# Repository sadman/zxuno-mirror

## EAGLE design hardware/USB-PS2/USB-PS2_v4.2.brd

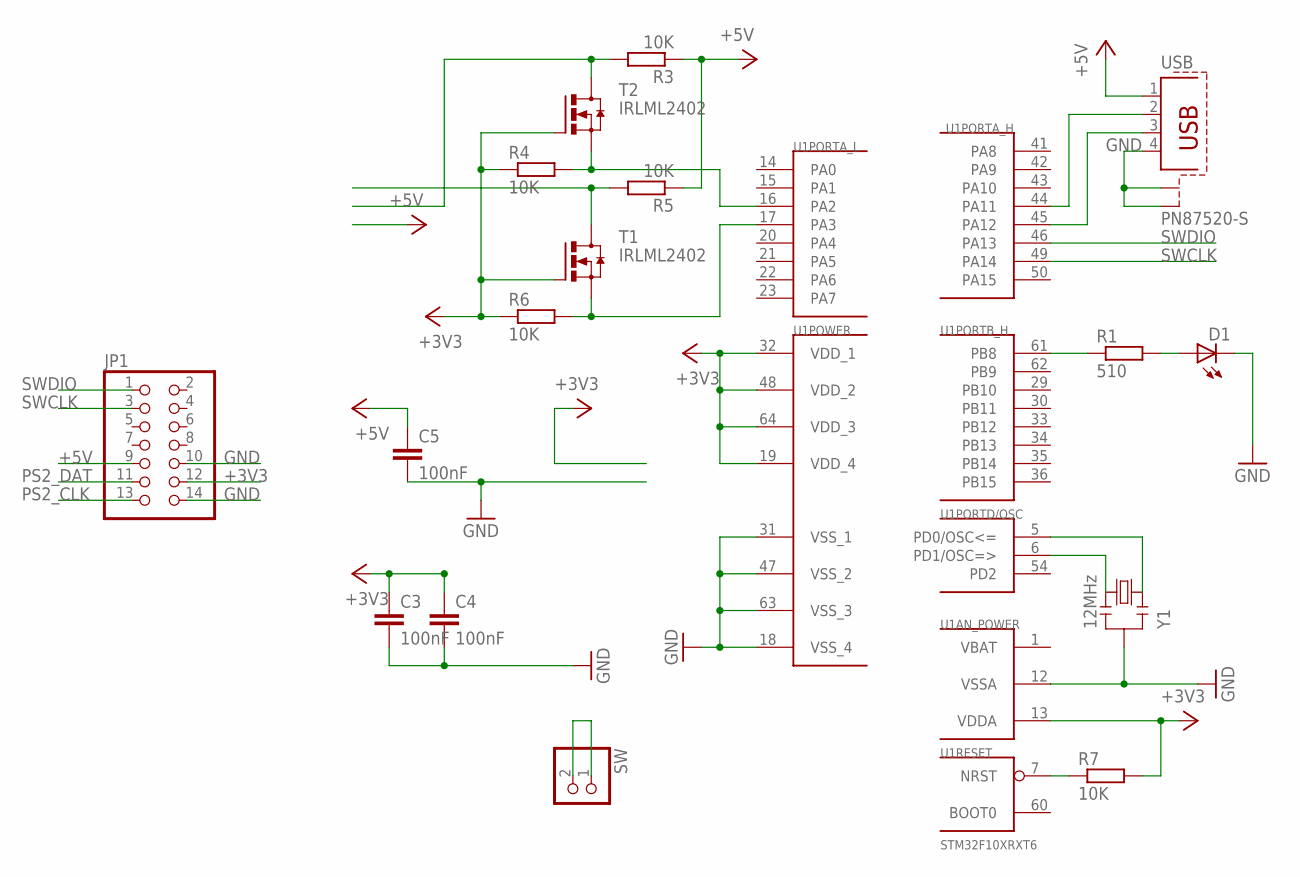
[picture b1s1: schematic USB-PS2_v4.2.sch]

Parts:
C3, C4, C5: 100nF; C0805
D1: LEDSML0805; SML0805
JP1: PINHD-2X7; 2X07
R1: 510; R0805
R3, R4, R5, R6, R7: 10K; R0805
SW: PINHD-1X2; 1X02
T1, T2: IRLML2402; MICRO3
U1: STM32F10XRXT6; TQFP64
USB: PN87520-S
Y1: 12MHz; RESONATOR

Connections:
+3V3: C3.1, C4.1, JP1.12, R4.1, R6.1, R7.2, T1.1 (G), T2.1 (G), U1.13 (VDDA), U1.19 (VDD_4), U1.32 (VDD_1), U1.48 (VDD_2), U1.64 (VDD_3)
+5V: C5.1, JP1.9, R3.1, R5.1, USB.1
GND: C3.2, C4.2, C5.2, D1.C, JP1.10, JP1.14, U1.12 (VSSA), U1.18 (VSS_4), U1.31 (VSS_1), U1.47 (VSS_2), U1.63 (VSS_3), USB.4, USB.S1, USB.S2, Y1.2
unnamed: U1.44 (PA11), USB.2
unnamed: U1.45 (PA12), USB.3
unnamed: R1.1, U1.61 (PB8)
unnamed: U1.5 (PD0/OSC<=), Y1.1
unnamed: D1.A, R1.2
unnamed: U1.6 (PD1/OSC=>), Y1.3
unnamed: R7.1, U1.7 (NRST)
unnamed: SW.1, SW.2
unnamed: R6.2, T1.2 (S), U1.17 (PA3)
unnamed: R4.2, T2.2 (S), U1.16 (PA2)
PS2_CLK: JP1.13, R5.2, T1.3 (D)
PS2_DAT: JP1.11, R3.2, T2.3 (D)
SWCLK: JP1.3, U1.49 (PA14)
SWDIO: JP1.1, U1.46 (PA13)
VBAT: U1.1 (VBAT)

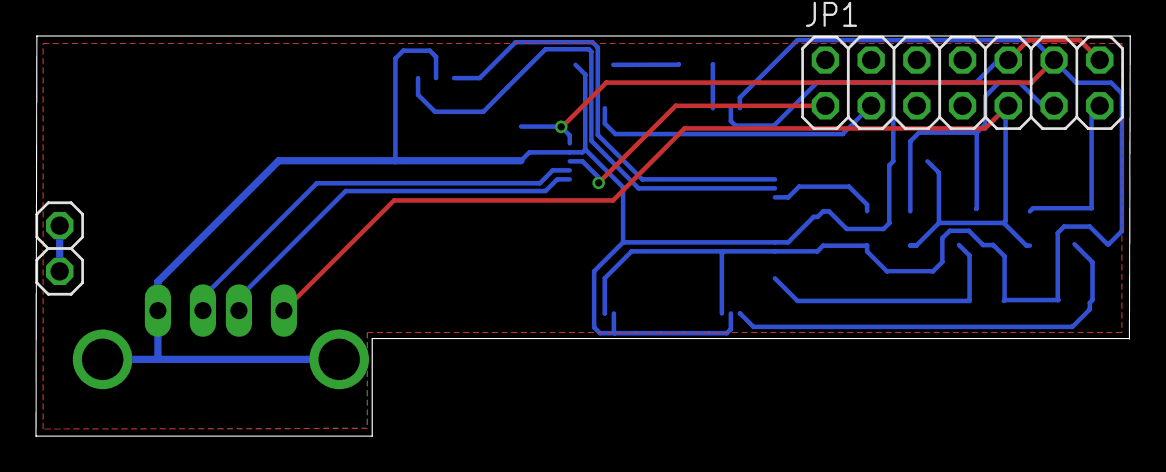
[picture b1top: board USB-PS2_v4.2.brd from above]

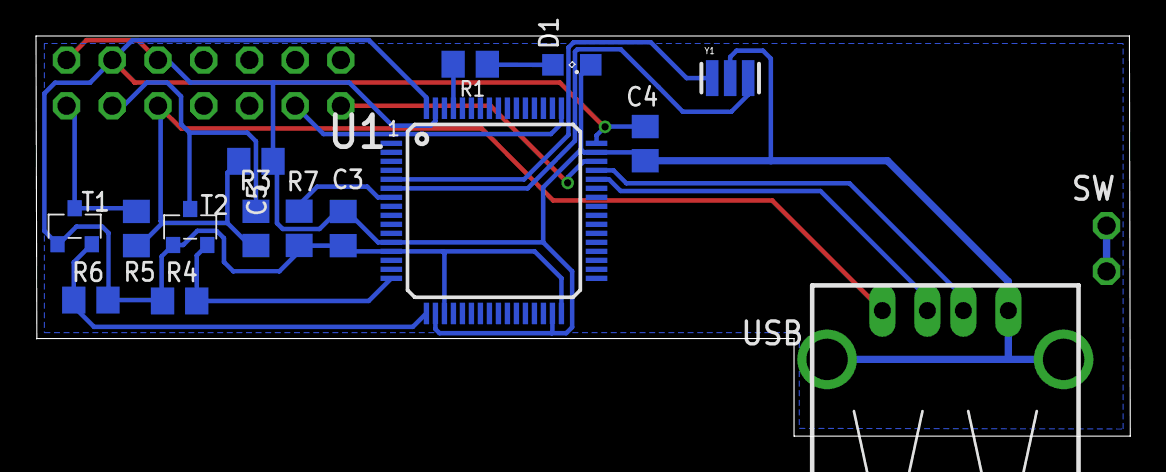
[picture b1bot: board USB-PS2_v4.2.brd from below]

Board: 2 copper layers, 60.8 x 22.2 mm, 17 parts (15 on the bottom side), 17 nets.

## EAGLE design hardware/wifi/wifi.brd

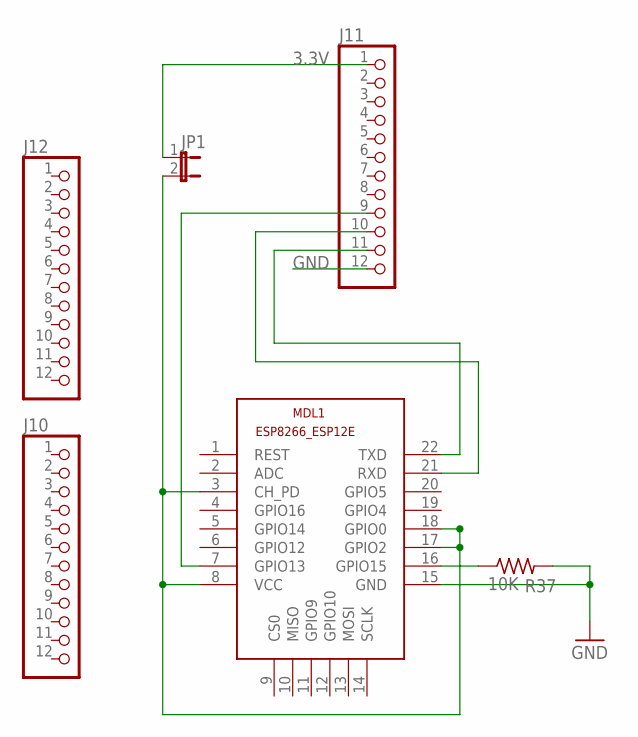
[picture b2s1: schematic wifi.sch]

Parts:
J10, J11, J12: PINHD-1X12; 1X12
JP1: JP1E; JP1
MDL1: ESP8266-12EESP8266-ESP12E; ESP8266-ESP12E
R37: 10K; R0805

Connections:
3.3V: J11.1, JP1.1
GND: J11.12, MDL1.15 (GND), R37.2
unnamed: MDL1.16 (GPIO15), R37.1
unnamed: J11.9, MDL1.7 (GPIO13)
unnamed: J11.10, MDL1.21 (RXD)
unnamed: J11.11, MDL1.22 (TXD)
VIN: JP1.2, MDL1.3 (CH_PD), MDL1.8 (VCC), MDL1.17 (GPIO2), MDL1.18 (GPIO0)

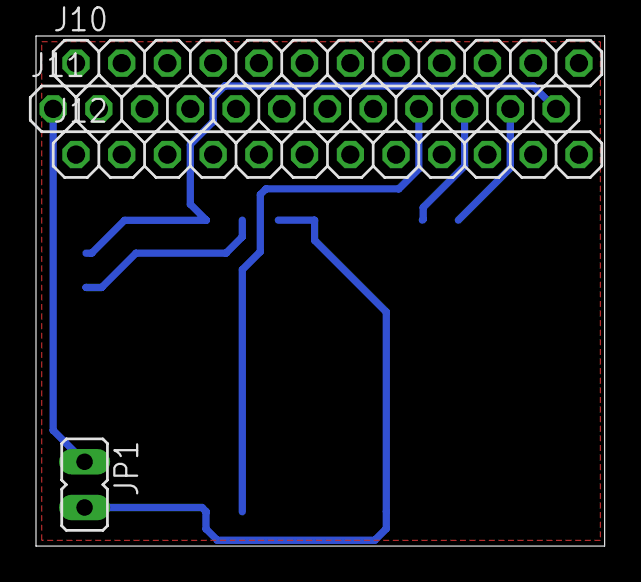
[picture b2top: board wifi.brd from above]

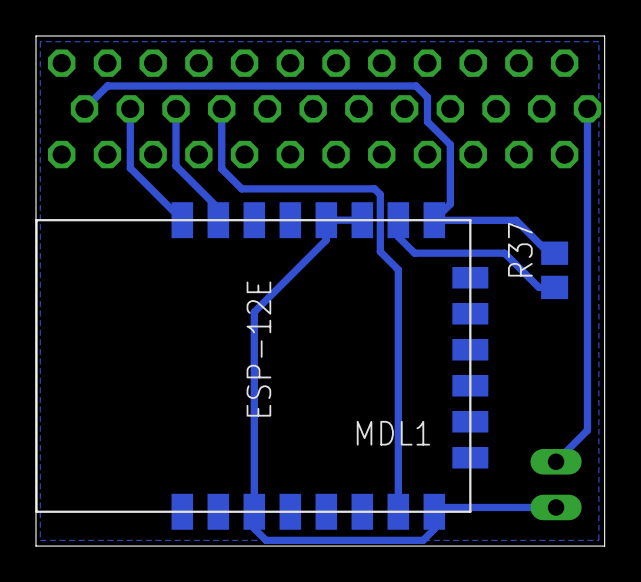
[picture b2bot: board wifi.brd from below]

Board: 2 copper layers, 31.6 x 28.3 mm, 6 parts (2 on the bottom side), 7 nets.

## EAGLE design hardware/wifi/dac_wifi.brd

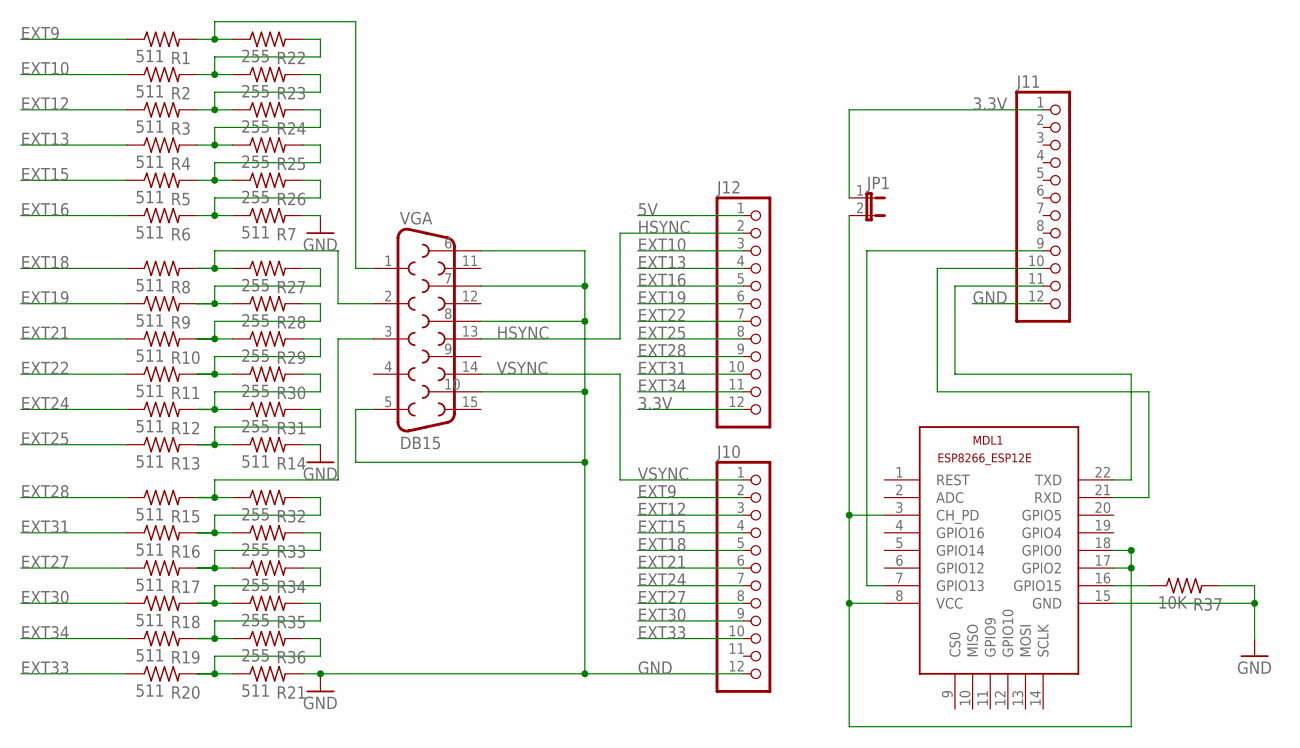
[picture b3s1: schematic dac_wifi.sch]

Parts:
J10, J11, J12: PINHD-1X12; 1X12
JP1: JP1E; JP1
MDL1: ESP8266-12EESP8266-ESP12E; ESP8266-ESP12E
R1, R2, R3, R4, R5, R6, R7, R8, R9, R10, R11, R12, R13, R14, R15, R16, R17, R18, R19, R20, R21: 511; R0805
R22, R23, R24, R25, R26, R27, R28, R29, R30, R31, R32, R33, R34, R35, R36: 255; R0805
R37: 10K; R0805
VGA: DB15

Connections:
3.3V: J11.1, J12.12, JP1.1
5V: J12.1
EXT9: J10.2, R1.1
EXT10: J12.3, R2.1
EXT12: J10.3, R3.1
EXT13: J12.4, R4.1
EXT15: J10.4, R5.1
EXT16: J12.5, R6.1
EXT18: J10.5, R8.1
EXT19: J12.6, R9.1
EXT21: J10.6, R10.1
EXT22: J12.7, R11.1
EXT24: J10.7, R12.1
EXT25: J12.8, R13.1
EXT27: J10.8, R17.1
EXT28: J12.9, R15.1
EXT30: J10.9, R18.1
EXT31: J12.10, R16.1
EXT33: J10.10, R20.1
EXT34: J12.11, R19.1
GND: J10.12, J11.12, MDL1.15 (GND), R7.2, R14.2, R21.2, R37.2, VGA.5, VGA.6, VGA.7, VGA.8, VGA.10
GREEN: R8.2, R27.1, VGA.2
HSYNC: J12.2, VGA.13
unnamed: MDL1.16 (GPIO15), R37.1
unnamed: J11.9, MDL1.7 (GPIO13)
unnamed: J11.10, MDL1.21 (RXD)
unnamed: J11.11, MDL1.22 (TXD)
unnamed: R20.2, R21.1, R36.2
unnamed: R9.2, R27.2, R28.1
unnamed: R2.2, R22.2, R23.1
unnamed: R1.2, R22.1, VGA.1
unnamed: R12.2, R30.2, R31.1
unnamed: R6.2, R7.1, R26.2
unnamed: R3.2, R23.2, R24.1
unnamed: R4.2, R24.2, R25.1
unnamed: R5.2, R25.2, R26.1
unnamed: R11.2, R29.2, R30.1
unnamed: R13.2, R14.1, R31.2
unnamed: R10.2, R28.2, R29.1
unnamed: R15.2, R32.1, VGA.3
unnamed: R16.2, R32.2, R33.1
unnamed: R17.2, R33.2, R34.1
unnamed: R18.2, R34.2, R35.1
unnamed: R19.2, R35.2, R36.1
VIN: JP1.2, MDL1.3 (CH_PD), MDL1.8 (VCC), MDL1.17 (GPIO2), MDL1.18 (GPIO0)
VSYNC: J10.1, VGA.14

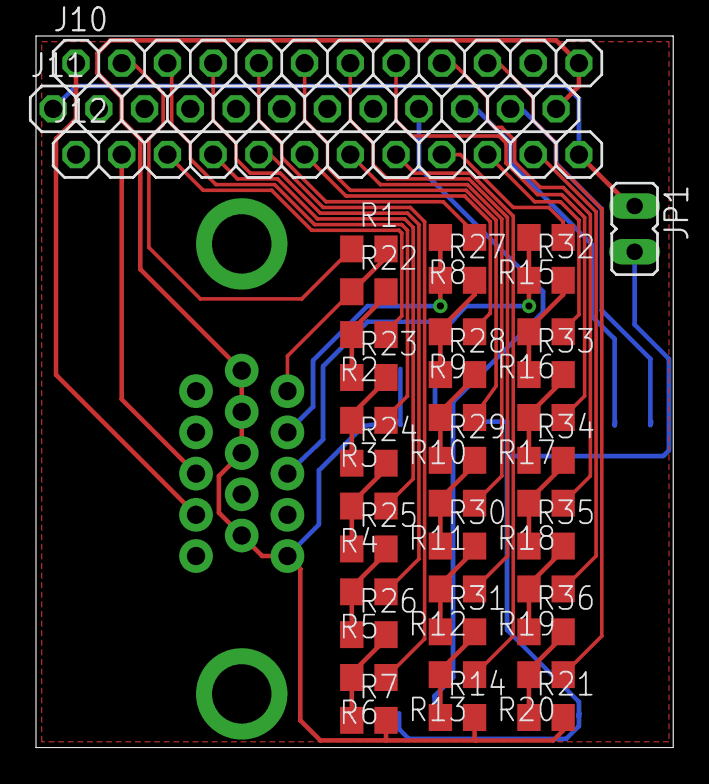
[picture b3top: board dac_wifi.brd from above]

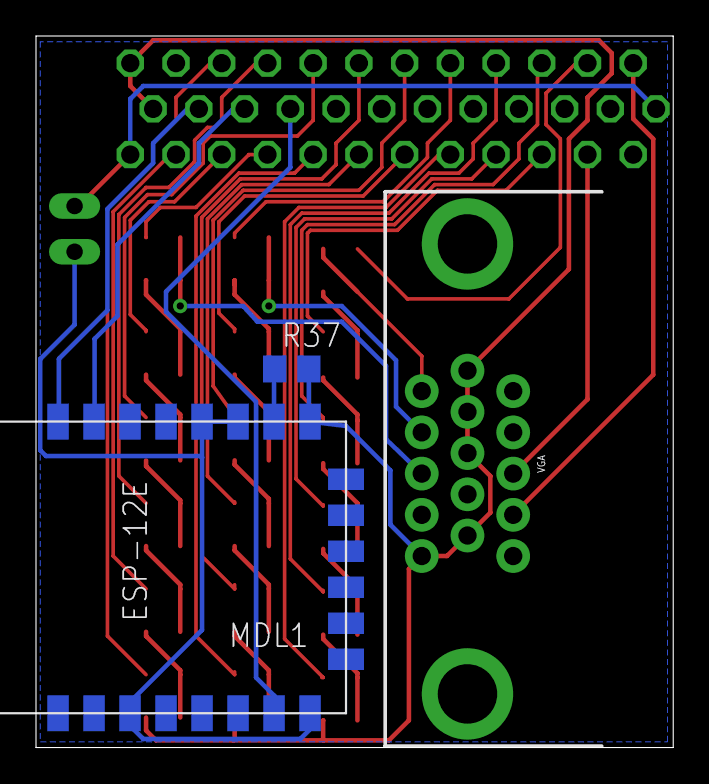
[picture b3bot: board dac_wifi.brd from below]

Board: 2 copper layers, 35.4 x 39.5 mm, 43 parts (3 on the bottom side), 45 nets.

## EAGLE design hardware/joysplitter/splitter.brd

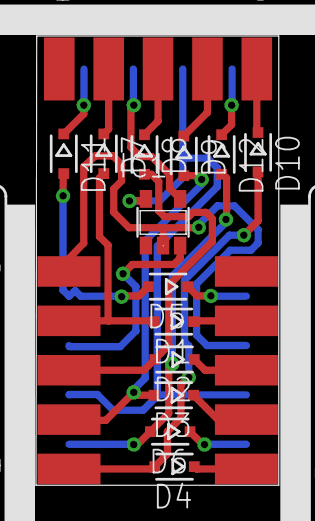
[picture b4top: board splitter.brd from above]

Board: 2 copper layers, 13.5 x 25.0 mm, 16 parts (0 on the bottom side), 22 nets.

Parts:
D1, D2, D3, D4, D5, D6, D7, D8, D9, D10, D11, D12: SOD323-R
IC1: 74LVC1G04DBV; SOT23-5
X1, X2: male; F09D
X3: female; F09D

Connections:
/SELECT: IC1.4, X2.7
DOWN: D3.A, D9.A, X3.2
FIRE1: D6.A, D12.A, X3.6
FIRE2: D5.A, D11.A, X3.9
GND: IC1.3, X3.8
LEFT: D2.A, D8.A, X3.3
unnamed: D2.C, X1.3
unnamed: D8.C, X2.3
unnamed: D1.C, X1.2
unnamed: D3.C, X1.4
unnamed: D7.C, X2.2
unnamed: D9.C, X2.4
unnamed: D10.C, X2.5
unnamed: D4.C, X1.5
unnamed: D6.C, X1.9
unnamed: D5.C, X1.6
unnamed: D12.C, X2.9
unnamed: D11.C, X2.6
RIGHT: D1.A, D7.A, X3.4
SELECT: IC1.2, X1.7, X3.5
UP: D4.A, D10.A, X3.1
VCC: IC1.5, X1.8, X2.8, X3.7

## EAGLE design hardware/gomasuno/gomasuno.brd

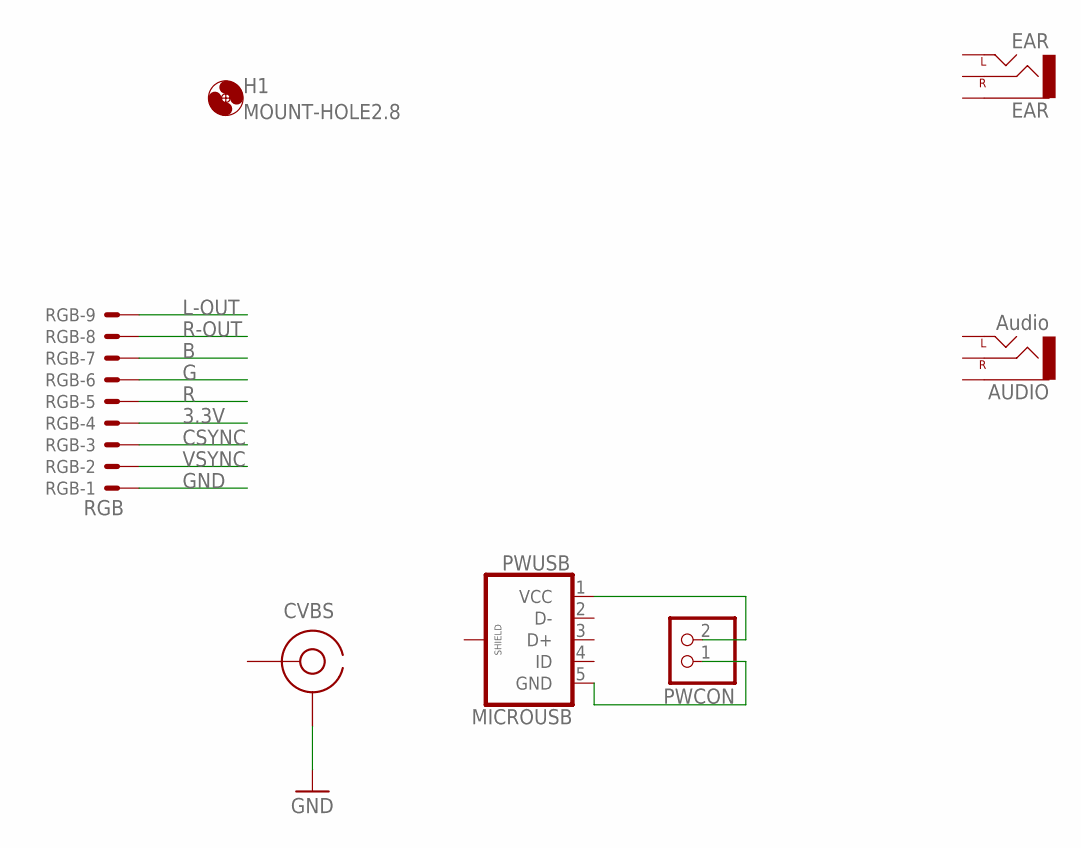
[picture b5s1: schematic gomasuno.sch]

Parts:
AUDIO: Audio; AUDIO-JACK
CVBS: RCA
EAR: EAR; AUDIO-JACK
H1: MOUNT-HOLE2.8; 2,8
PWCON: PINHD-1X2; 1X02
PWUSB: MICROUSB; MICRO_USB_1PRIMARY
RGB: RGB; 53048-09

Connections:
3.3V: RGB.4
B: RGB.7
CSYNC: RGB.3
G: RGB.6
GND: CVBS.GND, PWCON.1, PWUSB.5 (GND), RGB.1
L-OUT: RGB.9
unnamed: PWCON.2, PWUSB.1 (VCC)
R: RGB.5
R-OUT: RGB.8
VSYNC: RGB.2

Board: 2 copper layers, 7 parts (0 on the bottom side), 2 nets, no tracks yet.

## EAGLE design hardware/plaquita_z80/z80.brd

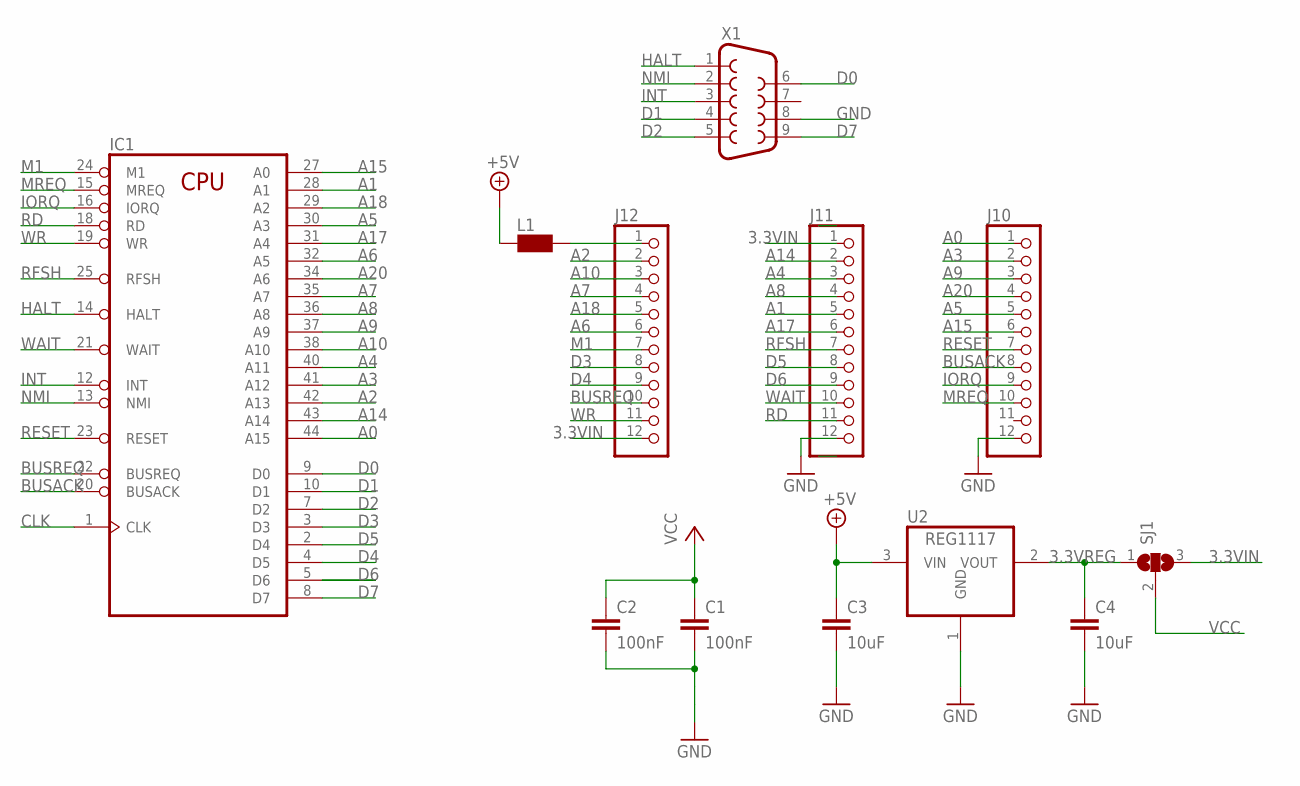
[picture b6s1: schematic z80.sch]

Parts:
C1, C2: 100nF; C0805K
C3, C4: 10uF; C0805K
IC1: Z80CPU-F; QFP-44
J10, J11, J12: PINHD-1X12; 1X12
L1: WE-CBF_0805; 0805
SJ1: SJ2W; SJ_2
U2: REG1117; SOT223
X1: F09D

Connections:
3.3VIN: J11.1, J12.12, SJ1.3
3.3VREG: C4.1, SJ1.1, U2.2 (VOUT)
+5V: C3.1, L1.2, U2.3 (VIN)
A0: IC1.44 (A15), J10.1
A1: IC1.28 (A1), J11.5
A2: IC1.42 (A13), J12.2
A3: IC1.41 (A12), J10.2
A4: IC1.40 (A11), J11.3
A5: IC1.30 (A3), J10.5
A6: IC1.32 (A5), J12.6
A7: IC1.35 (A7), J12.4
A8: IC1.36 (A8), J11.4
A9: IC1.37 (A9), J10.3
A10: IC1.38 (A10), J12.3
A14: IC1.43 (A14), J11.2
A15: IC1.27 (A0), J10.6
A17: IC1.31 (A4), J11.6
A18: IC1.29 (A2), J12.5
A20: IC1.34 (A6), J10.4
BUSACK: IC1.20 (BUSACK), J10.8
BUSREQ: IC1.22 (BUSREQ), J12.10
CLK: IC1.1 (CLK)
D0: IC1.9 (D0), X1.6
D1: IC1.10 (D1), X1.4
D2: IC1.7 (D2), X1.5
D3: IC1.3 (D3), J12.8
D4: IC1.4 (D5), J12.9
D5: IC1.2 (D4), J11.8
D6: IC1.5 (D6), J11.9
D7: IC1.8 (D7), X1.9
GND: C1.2, C2.2, C3.2, C4.2, IC1.26 (GND), J10.12, J11.12, U2.1 (GND), X1.8
HALT: IC1.14 (HALT), X1.1
INT: IC1.12 (INT), X1.3
IORQ: IC1.16 (IORQ), J10.9
M1: IC1.24 (M1), J12.7
MREQ: IC1.15 (MREQ), J10.10
unnamed: J12.1, L1.1
NMI: IC1.13 (NMI), X1.2
RD: IC1.18 (RD), J11.11
RESET: IC1.23 (RESET), J10.7
RFSH: IC1.25 (RFSH), J11.7
VCC: C1.1, C2.1, IC1.6 (VCC), SJ1.2
WAIT: IC1.21 (WAIT), J11.10
WR: IC1.19 (WR), J12.11

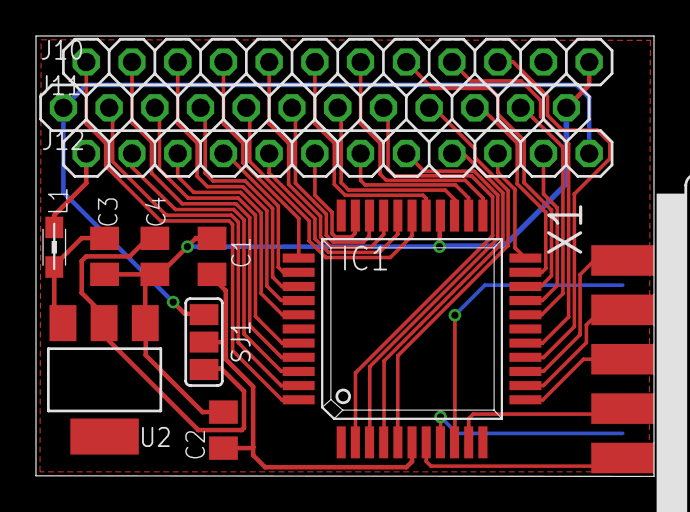
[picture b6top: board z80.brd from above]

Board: 2 copper layers, 34.3 x 24.5 mm, 12 parts (0 on the bottom side), 43 nets.

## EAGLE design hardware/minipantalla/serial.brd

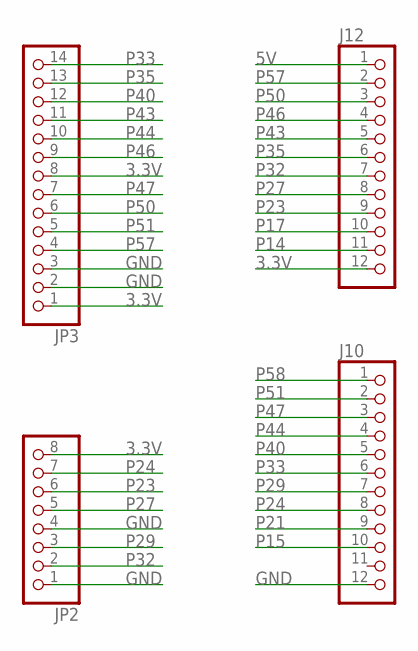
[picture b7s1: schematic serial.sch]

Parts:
J10, J12: PINHD-1X12; 1X12
JP2: PINHD-1X8; 1X08
JP3: PINHD-1X14; 1X14

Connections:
3.3V: J12.12, JP2.8, JP3.1, JP3.8
5V: J12.1
GND: J10.12, JP2.1, JP2.4, JP3.2, JP3.3
P14: J12.11
P15: J10.10
P17: J12.10
P21: J10.9
P23: J12.9, JP2.6
P24: J10.8, JP2.7
P27: J12.8, JP2.5
P29: J10.7, JP2.3
P32: J12.7, JP2.2
P33: J10.6, JP3.14
P35: J12.6, JP3.13
P40: J10.5, JP3.12
P43: J12.5, JP3.11
P44: J10.4, JP3.10
P46: J12.4, JP3.9
P47: J10.3, JP3.7
P50: J12.3, JP3.6
P51: J10.2, JP3.5
P57: J12.2, JP3.4
P58: J10.1

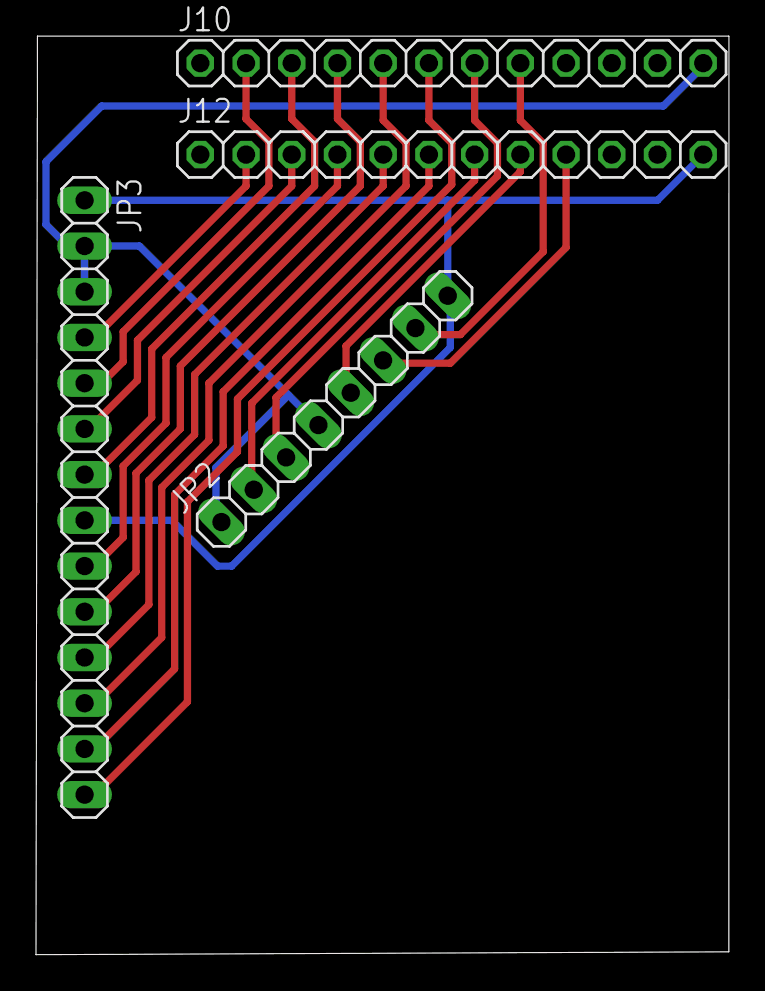
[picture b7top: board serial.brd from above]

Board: 2 copper layers, 38.5 x 51.0 mm, 4 parts (0 on the bottom side), 17 nets.

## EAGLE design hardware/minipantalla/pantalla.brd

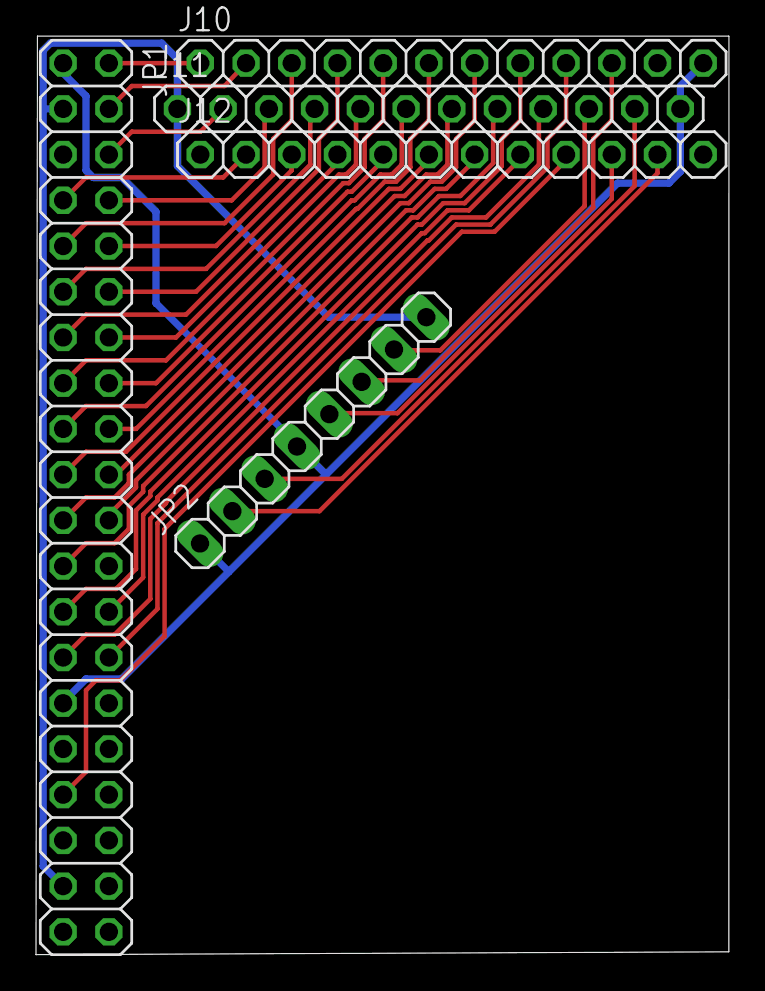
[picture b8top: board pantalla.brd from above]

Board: 2 copper layers, 38.5 x 51.0 mm, 5 parts (0 on the bottom side), 32 nets.

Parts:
J10, J11, J12: 1X12
JP1: 2X20
JP2: 1X08

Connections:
3.3V: J11.1, JP1.3, JP1.37, JP2.8
GND: J10.12, J11.12, JP1.1, JP1.29, JP2.1, JP2.4
P12: J11.11, JP2.3
P14: J12.11, JP2.2
P15: J10.10, JP2.6
P16: J11.10, JP2.7
P17: J12.10, JP2.5
P21: J10.9, JP1.28
P22: J11.9, JP1.27
P23: J12.9, JP1.33
P24: J10.8, JP1.25
P26: J11.8, JP1.23
P27: J12.8, JP1.26
P29: J10.7, JP1.21
P30: J11.7, JP1.20
P32: J12.7, JP1.22
P33: J10.6, JP1.18
P34: J11.6, JP1.17
P35: J12.6, JP1.19
P40: J10.5, JP1.15
P41: J11.5, JP1.14
P43: J12.5, JP1.16
P44: J10.4, JP1.12
P45: J11.4, JP1.11
P46: J12.4, JP1.13
P47: J10.3, JP1.9
P48: J11.3, JP1.8
P50: J12.3, JP1.10
P51: J10.2, JP1.4
P56: J11.2, JP1.6
P57: J12.2, JP1.7
P58: J10.1, JP1.2

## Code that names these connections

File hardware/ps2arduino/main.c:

/*
 *    Conversor teclado ZX-spectrum 8x5 -> PS/2 del ZX-UNO by Quest
 *
 *    Combinaciones especiales: 
 *    - Reset maestro = SYMBOL+CAPS+9
 *    - NMI = SYMBOL+CAPS+1
 */

#include <avr/io.h>
#include <inttypes.h>
#include <util/delay.h>
#include "keymaps.h"

#define LED_ON	PORTB |= (1<<5)		
#define LED_OFF	PORTB &= ~(1<<5)
#define LED_CONFIG	DDRB |= (1<<5) //Led en PB5 en Pro mini y similares

#define ZXUNO_RESET KEY_9 //tecla para el reseteo junto a shift+symbol (9)
#define ZXUNO_NMI KEY_1 //tecla para NMI junto a shift+symbol (space) (1)

////////Pro Mini
#define PS2_PORT	PORTC
#define PS2_DDR		DDRC
#define PS2_PIN		PINC

#define PS2_DAT		PC4
#define PS2_CLK		PC5

#define HI 1
#define LO 0
#define _IN 1
#define _OUT 0

//Definicion de pines y puertos en arrays

///////////Pro Mini
//{PC1, PC0, PB4, PB3, PB2};
uint8_t pinsC[COLS] =  {1, 0, 4, 3, 2};
uint8_t bcdC[COLS] =   {3, 3, 2, 2, 2};

//{PD2, PD3, PD4, PD5, PD6, PD7, PB0, PB1};
uint8_t pinsR[ROWS] =  {2, 3, 4, 5, 6, 7, 0, 1};
uint8_t bcdR[ROWS] =   {4, 4, 4, 4, 4, 4, 2, 2};

//Caps Shift (Shift)
#define SHIFT_COL 4  
#define SHIFT_ROW 5  

//Symbol(control)
#define SYMBOL_COL 3   
#define SYMBOL_ROW 7   

//combinacion reset (9)
#define RESET_COL 3
#define RESET_ROW 3

//combinacion NMI (1)
#define NMI_COL 4
#define NMI_ROW 0

void leds_debug(){
 	LED_ON;
	_delay_ms(60);
	LED_OFF;
	_delay_ms(30);
}

void pinSet(pin, bcd, stat) //stat 1 = in, stat 0 = out
{
     switch(bcd){
	case 2:  if (stat) DDRB &= ~_BV(pin); else DDRB |= _BV(pin); break;
        case 3:  if (stat) DDRC &= ~_BV(pin); else DDRC |= _BV(pin); break;
	case 4:  if (stat) DDRD &= ~_BV(pin); else DDRD |= _BV(pin); break;	  
     }
} 

uint8_t pinStat(pin, bcd)
{
     switch(bcd){
	case 2:  if (!(PINB & (1<<pin))) return 1; else return 0; break;
        case 3:  if (!(PINC & (1<<pin))) return 1; else return 0; break;
	case 4:  if (!(PIND & (1<<pin))) return 1; else return 0; break;	  
     }
  return 0;
}

void pinPut(pin, bcd, stat) //stat 1 = HI, stat 0 = LO
{
     switch(bcd){
	case 2:  if (!stat) PORTB &= ~_BV(pin); else PORTB |= _BV(pin); break;
        case 3:  if (!stat) PORTC &= ~_BV(pin); else PORTC |= _BV(pin); break;
	case 4:  if (!stat) PORTD &= ~_BV(pin); else PORTD |= _BV(pin); break;	  
     }
} 

void ps2Mode(uint8_t pin, uint8_t mode) 
{
    if(mode) { //high
	PS2_DDR &= ~_BV(pin); //input (Truco DDR. Como input sin estado, se pone en modo Hi-Z)
        //PS2_PORT |= _BV(pin);  //high
    } else { //low
        PS2_DDR |= _BV(pin); //output (Truco DDR. Como output, se pone a 0v)
        //PS2_PORT &= ~_BV(pin);  //low
    }
}

void ps2Init() 
{
  //ponemos en alto ambas señales
  PS2_PORT &= ~_BV(PS2_DAT); //A 0
  PS2_PORT &= ~_BV(PS2_DAT); //A 0
  ps2Mode(PS2_DAT, HI);
  ps2Mode(PS2_CLK, HI);
}

uint8_t ps2Stat()
{
  if (!(PS2_PIN & (1<<PS2_CLK)))
    return 1;
  if (!(PS2_PIN & (1<<PS2_DAT)))
    return 1;
    
  return 0;
}

//En us, reloj y semireloj, para los flancos
//zxuno v2 test15: CK1 = 240, CK2 = 480. Uso normal: CK1 = 20, CK2 = 40 
//(revertir a normal cuando el core ps/2 del ZX-UNO se mejore)
#define CK1 240 
#define CK2 480

//envio de datos ps/2 simulando reloj con delays.
void sendPS2(unsigned char code)
{
LED_ON;
        //Para continuar las líneas deben estar en alto
	if (ps2Stat())
		return;   
 
 	unsigned char parity = 1;
	unsigned char i = 0;
        
        //iniciamos transmisión
        ps2Mode(PS2_DAT, LO);
        _delay_us(CK1);
        
        ps2Mode(PS2_CLK, LO); //bit de comienzo
        _delay_us(CK2);
        ps2Mode(PS2_CLK, HI);
        _delay_us(CK1);
        //enviamos datos
        for (i = 0; i < 8; ++i) 
	{
	    if ((0b00000001 & code))
	      ps2Mode(PS2_DAT, HI);		
	    else
	      ps2Mode(PS2_DAT, LO);    		
	    
	    _delay_us(CK1);
            ps2Mode(PS2_CLK, LO);
            _delay_us(CK2);
            ps2Mode(PS2_CLK, HI);
            _delay_us(CK1);

        //paridad
            if ((0b00000001 & code) == 0b00000001) 
            {
                if (!parity)
                    parity = 1;
                else
                    parity = 0;
            }
    	    code = code >> 1;
	}

	// Enviamos bit de paridad
	if (parity)
	    ps2Mode(PS2_DAT, HI);		
	else
	    ps2Mode(PS2_DAT, LO);
        
	 _delay_us(CK1);
         ps2Mode(PS2_CLK, LO);
         _delay_us(CK2);
         ps2Mode(PS2_CLK, HI);
         _delay_us(CK1);
            
         //Bit de parada
         ps2Mode(PS2_DAT, HI);
         _delay_us(CK1);
         ps2Mode(PS2_CLK, LO);
         _delay_us(CK2);
         ps2Mode(PS2_CLK, HI);
         _delay_us(CK1);
         
         _delay_us(CK2*3); //fin
        
LED_OFF;
}

//codifica envio de caracteres ps/2 
void sendCode(unsigned char key, uint8_t shiftd, uint8_t symbold) 
{
  uint8_t extn = 0;
  unsigned char key_mod = KEY_LSHIFT; //si es shift suelto = shift, si es para reset = alt.

  //checkeamos si es una tecla con scancode extendido (E0)
  switch(key) {
    case KEY_LEFT:
    case KEY_DOWN:
    case KEY_RIGHT:
    case KEY_UP:
    case KEY_RALT:
    //case KEY_RCTRL:
       extn = 1; 
       shiftd = 0; //no dejamos hacer shift con flechas de momento
       break;
    case ZXUNO_RESET:
        if (shiftd && symbold) {
          key = KEY_DELETE;    
          key_mod = KEY_LALT;     
        }
        break;
    case ZXUNO_NMI:
        if (shiftd && symbold) {
          key = KEY_F5;    
          key_mod = KEY_LALT;     
        }
        break;        
    default:
       extn = 0; 
       break;
  }
//secuencia  
  if (shiftd) 
    sendPS2(key_mod);
  
  if (symbold) 
    sendPS2(KEY_LCTRL);
  
  if (extn) 
    sendPS2(0xE0);
   
 if (key)
  sendPS2(key);
  
  if (extn)
    sendPS2(0xE0);
  
  if (key) 
   sendPS2(0xF0);

 if (key)
  sendPS2(key);
   
  if (symbold) {
    sendPS2(0xF0);
    sendPS2(KEY_LCTRL);
  }    
  
  if (shiftd) {
    sendPS2(0xF0);
    sendPS2(key_mod);
  }
  
//fin secuencia
}

void pressKey(uint8_t r, uint8_t c, uint8_t shiftd, uint8_t symbold)
{  
  if (shiftd || symbold)
  {
    uint8_t key;

    if (shiftd)
      key = mapShift[r][c];
    if (symbold)
      key = mapSymbol[r][c];

    if (key)
      sendCode(key,0,0);
    else
    {
      key = mapZX[r][c];
      if (key)
        sendCode(key,shiftd,symbold);
    }
  }
  else
  {
    uint8_t key = mapZX[r][c];
    if (key)
      sendCode(key,0,0);
  }
}

//preparamos matriz teclado.
void matrixInit()
{
   uint8_t c, r;
    
  LED_CONFIG;
  LED_OFF;

  for (c=0;c<COLS;c++)
  { 
    pinSet(pinsC[c],bcdC[c],_IN);
    pinPut(pinsC[c], bcdC[c], HI);
  }

  for (r=0;r<ROWS;r++)
    pinSet(pinsR[r],bcdR[r],_IN);
}

void matrixScan()
{
 
  uint8_t shiftd = 0;
  uint8_t symbold = 0;
  uint8_t prereset = 0;
  uint8_t prenmi = 0;
  uint8_t keyPressed = 0;
  uint8_t r, c;

//Combinaciones especiales
  //pulsacion shift
  pinSet(pinsR[SHIFT_ROW],bcdR[SHIFT_ROW],_OUT);  
 _delay_us(5);
   if(pinStat(pinsC[SHIFT_COL], bcdC[SHIFT_COL]))
    shiftd = 1;
  pinSet(pinsR[SHIFT_ROW],bcdR[SHIFT_ROW],_IN);
 _delay_us(5);

  //pulsacion symbol  
  pinSet(pinsR[SYMBOL_ROW],bcdR[SYMBOL_ROW],_OUT);  
 _delay_us(5);
  if(pinStat(pinsC[SYMBOL_COL], bcdC[SYMBOL_COL])) 
    symbold = 1;  
 _delay_us(5);
  pinSet(pinsR[SYMBOL_ROW],bcdR[SYMBOL_ROW],_IN);

  //ver si es reset
  if (shiftd && symbold && !keyPressed) {
    pinSet(pinsR[RESET_ROW],bcdR[RESET_ROW],_OUT);
 _delay_us(5);
    if(pinStat(pinsC[RESET_COL], bcdC[RESET_COL]))
      prereset = 1;  
    pinSet(pinsR[RESET_ROW],bcdR[RESET_ROW],_IN);

 _delay_us(5);
    
    pinSet(pinsR[NMI_ROW],bcdR[NMI_ROW],_OUT);
 _delay_us(5);
    if(pinStat(pinsC[NMI_COL], bcdC[NMI_COL]))
      prenmi = 1;  
    pinSet(pinsR[NMI_ROW],bcdR[NMI_ROW],_IN);
  

    if (prereset)
       sendCode(ZXUNO_RESET,shiftd,symbold); //zxuno reset
    else 
      if (prenmi)
         sendCode(ZXUNO_NMI,shiftd,symbold); //zxuno nmi 
       else  
         sendCode(0,shiftd,symbold); //extended mode  
  }

//Escaneo de filas
  for (r=0;r<ROWS;r++)
  {
    //activar fila
    pinSet(pinsR[r],bcdR[r],_OUT);
    pinPut(pinsR[r], bcdR[r], LO);
    _delay_us(5);
    for (c=0;c<COLS;c++)
    { 
        if((pinStat(pinsC[c], bcdC[c]))) 
        {
	   _delay_us(10); //debounce
	   if((pinStat(pinsC[c], bcdC[c]))) 
	   {	
	     keyPressed = 1;          
	     pressKey(r, c, shiftd, symbold);      
	   }
    	}
   }
    //desact. fila
    pinSet(pinsR[r],bcdR[r],_IN);
  }
 //fin escaneo de filas

  pinPut(pinsR[SHIFT_ROW], bcdR[SHIFT_ROW], LO);
  pinPut(pinsR[SYMBOL_ROW], bcdR[SYMBOL_ROW], LO);

  //if (keyPressed)
    _delay_ms(100);

}

int main() 
{
	matrixInit();
	ps2Init();
	while(1) {
	  matrixScan();
	}
}

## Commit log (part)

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2016-05-22 Sigo haciendo commit desde el tren. Estoy probando con dos formas diferentes de generar los relojes del sistema. Este commit usa el PLL para generar los 3 relojes derivados del reloj principal de 28M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
2016-05-22 Muevo roms a carpeta rom_binaries
2016-05-22 Revierto cambios
2016-05-23 The interface with the SRAM from the new memory manager is now registered. Removed the requisite of non being in all-RAM mode to use the Timex MMU.
    Added decoding of bit 0 to avoid clashing with port $F4 when using an 8-bit OUT instruction, which puts the value of A in t he address bus high order bits.
    Removed 28MHz CPU support. It caused clock signals to be poorly routed. Have to finish reading the UG612 document from Xilinx about Timing Closure, as well as the document about how to put area const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
    The only odd thing you may find here is that I no longer generate all clocks from the PLL module, but only the master clock, 28 MHz. The remaining clocks are generated using a frequency d
2016-05-23 Actualizo web y cambio upgrade para que procese ROMS.ZX1
2016-05-23 Pongo variable que pide McLeod en $8fd5
2016-05-27 Borrador Chloe para Andrew Owen
2016-06-01 Add support for v2 boards, as I am testing one of them :)
2016-06-01 Backporting to v2 boards, at least, trying to. The boot ROM needs to be rewritten to be the old version, with non quad support, as quad pins were not wired to the FPGA.... or were they? Need to talk 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
2016-06-02 Modifico generamcs.bat para generar ROMS.ZX1
2016-06-15 Arreglo bug detectado por mad3001
2016-06-15 Muevo utilidades actualizado ROMs a carpeta spiflashutils
2016-06-15 Actualizo GenRom, leyendas incorrectas de param2 y cambio t por 2 en DITAY
2016-06-16 Arreglo bugs
2016-06-17 Actualizo genFlash.asm
2016-06-17 Finalizo sna2rom
2016-06-18 Añado nuevo core SMS test4 para todas las placas.
2016-06-24 Posiblemente, el commit final del TEST21, al menos para la v4.
    - Se arregló el problema de los cuelgues al arrancar del +3e. Era culpa de un bloque if-else if en la parte en la que se escribe en el registro 7FFD, que no estaba bien escrito y no se convertía a un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
    - Se han añadido tres registros al pool de registros del ZXUNO: DEVCONTROL, DEVCTRL2 y RADASCTRL. Ver Wiki para detalles.
    - Se ha aumentado el espacio en la boot ROM a 8KB para alojar código extra pendiente de desarrollar
    - IMPORTANTE! A partir de ahora ya deja de funcionar el sistema antiguo por el que se conmuta al modo radastaniano. Para conmutar al modo radastaniano hay que usar el registro RAD
2016-06-24 |Se han actualizado todos los programas y demos para que usen la nueva forma de acceder al modo radastaniano
2016-07-04 Actualizo firmware y GenRom
2016-07-05 Corrijo bug en generamcs.bat
2016-07-05 Actualizo generamcs.bat
2016-07-05 Apunto bien a core de SMS en generamcs.bat
2016-07-14 TEST 22 Intento averiguar por qué Scroll Lock no funciona bien la primera vez que se entra a la BIOS desde un poweron. Lo ultimo que he probado es a poner un detector de flanco positivo para la señal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
2016-07-14 TEST 22 fixed! Scroll Lock toggles between VGA 60Hz and RGB 15kHz New bootloader version (8KB) Keymaps fixed too (sorry about that)
2016-07-14 TEST 5. Added Ctrl-Alt-BkSpace to return to BIOS Added video output detection to automatically switch to VGA or RGB Added XCF file with timings Still no timing closure :(
2016-07-22 Añado backup.asm
2016-07-24 Añado Eagle sin verificar del USB Blaster
2016-07-24 Borro las utilidades que había aquí. Ahora están en /software/upgrade
2016-07-26 Añado una versión nueva de unoedge partiendo de la idea CPLD de McLeod
2016-07-26 Arreglo bug en ROMSUPGR detectado por carmeloco
2016-07-26 del todo
2016-07-28 Sigo los planes iniciales sin multiplexar pulsadores/switches
2016-07-28 Finalizo ruteado
2016-07-28 ajusto borde para que encaje mejor
2016-07-29 Pongo valores correctos de resistencias
2016-07-31 Roto chip para añadir GCLK
2016-07-31 Creo que ya está
2016-08-01 Añado nueva utilidad para gestionar archivos ROMS.ZX1: ZX-UNO RomPack Tool
2016-08-01 Añado pasivizator3
2016-08-01 Actualizo firmware a v0.47
2016-08-02 Arreglo CRC
2016-08-03 Actualizo documentación formato flash
2016-08-03 Aclaración de parte del formato TAP
2016-08-06 Continuación unoedge
2016-08-06 Actualizo ruteado de trainer2
2016-08-07 Actualizo trainer2
2016-08-07 Penúltimo avance trainer
2016-08-10 Agrego logos
2016-08-17 Primeras pruebas con este core. El teletipo funciona y estoy con el updater.
2016-08-19 Test completo, con pequeña modificacion en los valores que se escriben a la SRAM para detectar mejor puentes en el bus de datos y/o direcciones.
2016-08-24 Vuelvo a la antigua versión de esxdos
2016-09-01 BBC Micro core update: fixed Erst, fixed DAC input, video mode key (ScrollLock), scanlines option, video mode detection from main core, added Master Reset.
2016-09-02 Añado conectores y separo placa para que quepa en 10x10cm
2016-09-02 Paso a through hole
2016-09-03 Empiezo ruteado
2016-09-03 Me faltan 16 líneas
2016-09-04 Añado potenciómetros
2016-09-04 Añado iRepair
2016-09-06 Updated Apple II+ core: added 16k+128k ram card, new rewriten ps/2 core, improved reset, added keys for new functions: - scanlines, * mono / color display, added Master Reset key combo, fixed joy btn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
2016-09-06 Added ZX1 binary for BBC Micro core
2016-09-06 Desconecto WR y lo pongo a VCC en iFrom
2016-09-10 Small update to NES core: Added Master Reset combo to return to default Spectrum core, Added mappers and last fixes from the mist port. Added ZX1 binary for core upgrade.
2016-09-13 Borro ficheros esxdos
2016-09-15 Se ha cambiado por completo la forma en la que se generan los sincronismos compuestos para los modos de video compuesto y RGB. VGA no se ha tocado.
    Ahora el pulso de sincronismo vertical no es un pulso, sino un tren de pulsos conforme a lo que se recoge en este documento acerca de cómo generar una señal PAL progresiva "legal":
    http://martin.hinner.info/vga/pal.html
    Todo el código nuevo está en pal_sync_generator.v . Se siguen generando los pulsos horizontal y vertical, como antes, pero en lugar de derivar el sincronismo compuesto a partir de ellos, se genera de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
2016-09-16 Ajustes minimos en los valores iniciales para los registros de offset de sincronismo.
    Bit 5 de SCANDBLCTRL ahora se usa para elegir entre sincronismos tipo Spectrum o sincronismos estandar de PAL
2016-09-18 Added new Atari 800XL core ZX1 binary
2016-09-20 Añadida BIOS 0.55 en formato .ZX1 para actualizar por SD, e instrucciones.
2016-09-24 Añado pdf
2016-09-26 Añado versión antigua de ComCon
2016-09-28 Renombro generamcs.bat por generaflash.bat y quito la parte que genera .mcs
2016-10-11 Añado joysplitter
2016-10-12 Finalizo diseño
2016-10-30 Termino ruteado del addon HDMI
2016-11-02 Últimas correcciones de yombo
2016-11-04 Pongo jumper para desactivar alimentación del ESP12E
2016-11-05 Actualizaciones web de Hark0
2016-12-02 Añado diseño en Altium del A++
2016-12-10 Finalizo placa
2016-12-12 Actualizo huella para que incluya agujeros
2016-12-12 Organizo addons HDMI
2016-12-30 Añadidas varias versiones de ESXDOS para tenerlas a mano, y el programa SD Exerciser para probar compatibilidad con varias tarjetas SD
2017-01-01 Se han ordenado los directorios para soportar diferentes revisiones de la placa. Añadido proyecto ISE para proto v2. Añadidos ficheros COREx.ZX1 para placa v4 y v2.
2017-01-08 Corregido un error que hacia que colisionaran el puerto 0xF4 del Timex y el 0x7FFD del 128K, resultando en que los programas que quisieran usar a la vez cosas del Timex y del 128K no funcionaran bien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
2017-01-11 borrando archivos innecesarios en 01
2017-01-11 borrando archivos innecesarios en 03
2017-01-11 borrando archivos innecesarios en 03b
2017-01-11 borrando archivos innecesarios en 04b
2017-01-28 Primeras pruebas con el core del Chloe280SE. En concreto, se esta probando el nuevo core de Z80, unas 4-8 veces más rapido que el Z80, a la misma frecuencia de reloj.
2017-01-30 Añado sd2iec
2017-01-30 Renombro a ArdUNO
2017-02-01 Actualizo varios
2017-02-01 Actualizo firmware.asm
2017-02-04 Añadido interface de sonido Specdrum, en puerto de escritura 223d ($DF). Pendiente de testeo por si colusionia con algún otro dispositivo.
2017-02-11 Implementado un registro en el puerto $F7 para configurar el estereo. A documentar en wiki. Por defecto, la configuración es ACB con beeper y SpecDrum sonando por los dos canales.
    Se ha corregido un fallo menor que hacía que el bit 6 (MAPRAM) del registro de control de DivMMC se pusiera a 0 cuando uno quisiera, cuando esto no es así. Según el modelo de programación, una vez qu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
    Hay una discursión activa en el foro sobre si MAPRAM a 1 implica que se pagine directamente la RAM 3 a la dirección $0000 y siguientes. Según lo que entiendo del documento del modelo de programación,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
2017-02-14 Updated BBC Micro core. Initialization fix for Castle Quest. Added Joystick1 emulation. Changed clocks to 2 DCMs.
2017-02-14 Updated: Atari800XL sources
2017-02-14 Updated: Atari800XL binaries. New version 20171402, minor changes: added video mode detection from SRAM (bios), joypad emulation in numpad (5 and 2 down, 0 fire), Master reset also works with right a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
2017-02-18 Limpieza de ficheros antiguos en fuentes core XT
2017-02-24 Añado nuevas utilidades para Q128
2017-02-26 actualizo z80
2017-03-02 Nuevo mezclador. Sin necesidad de compresor. Espero que esta sea la última vez que necesito actualizarlo.
2017-03-07 Termino de subir los cambios para EXP25, con el .BIT y los ficheros .ZX1 para quien quiera probar el core.
2017-03-09 Finalizo pantalla
2017-03-09 Actualizado DMAPLAYW de acuerdo con las nuevas especificaciones del engine DMA
2017-03-10 Pequeña corrección en los timings del prescaler para esta aplicación, y añadir un WAV nuevo mu chulo.
2017-03-12 Arreglo bug en Manic Miner
2017-03-13 Versión preliminar, que es un ZX-Uno sólo con las huellas a reutilizar
2017-04-18 Actualizo FIRMWARE.ZX1 a 0.61
2017-04-18 Pongo link en version.txt del core MSX
2017-04-18 Añado el core de Amstrad CPC al directorio stable/binaries y a la zona de descargas
2017-04-20 Añadido addon multivideo a sugerencia de Uto
2017-06-12 Arreglo bug de velocidad
2017-06-13 Añado placas wifi
2017-06-21 Added some Arcade cores sources (NO roms included)
2017-06-21 Dummy RTC.SYS to be stored in the \SYS directory of the SD card. This won't give you a Real-Time Clock. It's just to get rid of the ERROR message when ESXDOS tries to load RTC.SYS.
    This module always returns the same date and time. You can change them and assemble (as binary file) with PASMO to get your own "date-personalized" RTC.SYS moodule.
2017-06-21 Updated SMS core source test5_multi. Added parametric support for: 1 Joy, 2 Joys-Splitter, 2 Joys-MFH-2M. Timing bugfixes. Fixes glitches as Vigilante has in RGB/Vcomp mode.
2017-06-25 Añado fuentes core jepalza zx80yuno
2017-07-01 Actualizo los cores de Oric, Apple2 y VIC20 con los errores de teclado corregidos por spark2k06 y neuro_999
2017-07-13 TEST 0 del Chloe. En realidad no es un core del sistema. Sólo pruebo un g enerador de video NTSC y al final me he emocionado poniéndole cositas a ver cómo se ve :D
2017-08-02 Añado cores de neuro_999
2017-08-29 Añado proyecto USB-PS2
2017-08-29 Añadidas las atribuciones de Quest en los fuentes
2017-11-09 Actualizo bitstream bbc micro que faltaba (compilado por azesmbog)
2017-12-13 Añado juego de dominio público para C64 Paku Paku, a petición de mapache
2017-12-17 Añado versión .TAP para recovery
2018-01-27 Actualiado LOADPZX para usar los nuevos registros para el lector de PZX.
2018-02-05 .JOYCONF con soporte para las nuevas funciones de joysticks en el core de spectrum (A partir de versión EX2B y próximo EXP26 en adelante).
    - Soporte para 2 botones en todos los protocolos (DB9)
    - Soporte nuevo protocolo OPQASPACEM
2018-02-12 Añado utilidad corebios.asm
2018-02-13 Añadido codigo fuente de la demo técnica BAD APPLE 2
2018-02-23 Actualizo core y bios en /stable/binaries
2018-04-03 Añado herramienta GOLDEN8
2018-05-30 Small update to fix Derby++ ROM behaviour with DivMMC, paging 48K ROM as ROM 1 instead of ROM 3 when using the 64K version of Derby++
2019-03-12 Subo core estable
2019-04-23 Recupero el Manic Miner, que no sé por qué lo borre. Mi memoria ya no es lo que era antes...
2019-09-15 EXP27, 15/9/2019. Pentagon implementation complete. ULA snow for 48K ULA complete.
2020-02-24 AY-3 core written from scratch.
2020-02-26 Updated strategy for latest core.
2020-03-05 Arreglado el Timex HiRes, que se escogorció al principio de EXP27
2020-03-07 XCF mejorado con especificacion de ciclos multipath.
2020-03-07 Definitivamente, se queda 28 MHz como máxima frecuencia.
2020-03-30 Small update to fix wrong parameter, that didn't allow the UART to work at the intended bps
2020-07-16 ZXDOS (LX25) support. Z80 WR_n timing fixes. Changes in T80 top level module to drop bidir buses and use instead two separate data buses.
2020-08-16 Commit gordo del último EXP27 con las versiones para todas las plataformas. Me falta por sintetizar LX16 y A35T.

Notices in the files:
hardware/gomasuno/gomasuno.brd:
(C)2017 ZX-Uno Team
hardware/plaquita_z80/z80.brd:
(C)2015 mcleod_ideafix
parts and their libraries:
SparkFun-Connectors: Licensing: Creative Commons ShareAlike 4.0 International - https://creativecommons.org/licenses/by-sa/4.0
SparkFun-Connectors: Licensing: CC v3.0 Share-Alike You are welcome to use this library for commercial purposes.
